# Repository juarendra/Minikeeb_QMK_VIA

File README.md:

# Minikeeb
a split keyboard mini based on microdox and microredox using MX Style Switch 

## Table of Content
* [Product Specsification](#product-specsification)
* [Download VIA](#download-via)
* [Load JSON File](#Load-JSON-File)
* [Link Keycode QMK](#Link-keycode-qmk)
* [Tutorial VIA Usage](#tutorial-via-usage)
* [Cara Setting Knob](#cara-setting-knob)
* [How To use MACRO](#how-to-use-macro)
* [Preview Hardware](#preview-hardware)
* [Preview VIA](#preview-via)
* [Cara Update/Upgrade Firmware](#cara-update/upgrade-firmware)
* [Documentation](#documentation)
  * [Pinout Diagram](#pinout-diagram)
  * [Dimension](#dimension)
  * [BOM](#bom)
  * [Schematic](#schematic)
  * [Example Program](#examples-program)
* [FAQ](#FAQ)

## Product Specsification
- Arduino Pro Micro Type C as Microcontroller
- QMK Firmware
- Support VIA, all key and knob can proggrammed
- RGB per Keys
- 4x Layer 
- Hotswap Switch
- 3D Case 

## Download VIA
Link Download VIA(CHOSEE BASED YOUR OS) : https://github.com/the-via/releases/releases
VIA WEB VERSION : https://usevia.app/

## Link Keycode QMK
- mouse : https://github.com/qmk/qmk_firmware/blob/master/docs/feature_mouse_keys.md
- keyboard : https://github.com/qmk/qmk_firmware/blob/master/docs/keycodes.md

## Tutorial VIA Usage
- https://docs.keeb.io/via

## Cara Setting Knob
- Untuk melakukan setting di knob perlu memasukan command berupa keycode qmk, Jadi cara nya sama dengan melakuykan setting dengan Any key seperti petunjuk pada link berikut: 
https://docs.keeb.io/via

Here's some examples:

- LALT(KC_TAB) - Sends Alt-Tab
- LCTL(KC_C) - Sends Ctrl-C
- LGUI(KC_C) - Sends Cmd-C or Win-C
- LSFT(LCTL(KC_END)) - Sends Shift-Ctrl-End
- MO(1) - Momentarily turn on layer 1
- LCA(KC_DEL) - Sends Ctrl-Alt-Del
- MT(MOD_RSFT, KC_ENT) - Sends Shift if held, Enter if tapped
- MACRO (0) - macro 0

## How To use MACRO
you can read on [this file](https://github.com/juarendra/STREAMPAD-QMK-VIA/blob/main/DOC/MACRO%20VIA%20USAGE.pdf)
or you can read on this [web](https://www.keychron.com/blogs/archived/how-to-use-via-to-program-your-keyboard)
or you can see video [youtube](https://youtu.be/GtSeo69Y0Zw)

## Preview Hardware

## Preview VIA

https://github.com/juarendra/Zeapad-Pro-QMK-VIA/assets/43043633/afd7e68e-0a54-4b18-be12-b96c0f13611a

## Cara Update/Upgrade Firmware
- Siapkan dahulu Keyboard minikeeb, kabel usb dan firmware yang ingin di update/upgrade ke keyboard anda anda
- Anda perlu melakukan flashing di masing masing sisi keyboard (kanan dan kiri)
- Siapkan Firmware yang akan digunakan untuk update/upgrade
- Download Software QMK Toolbox di [link berikut](https://github.com/qmk/qmk_toolbox/releases)
- Install Software QMK Toolbox, Install Semua drivernya. setelah siap anda dapat meload Firmware yang seblumnya. Lalu Centang Auto-Flash seperti gambar dibawah

- Lakukan flashing pada sisi kiri dahulu
- Pada minikeeb sisi kiri Colok kabel ujung usb type C ke keyboard tanpa mencolokannya dahulu ke USB PC anda
- Tekan dan tahan tombol yang berada di ujung atas kiri. lalu colokan Ujung USB yang sebelum ke USB PC anda sambil tetap menahan tombol sebelum nya sebentar
- Setelah ada bunyi/notif USB masuk. anda dapat melepaskan tombol/knobnya
- Maka secara otomatis macropad akan terflash. jika selesai maka tampilan QMK toolbox akan seperti gambar dibawah

- Lakukan flashing pada sisi kanan
- Pada minikeeb sisi kanan Colok kabel ujung usb type C ke keyboard tanpa mencolokannya dahulu ke USB PC anda
- Tekan dan tahan tombol yang berada di ujung atas kanan. lalu colokan Ujung USB yang sebelum ke USB PC anda sambil tetap menahan tombol sebelum nya sebentar
- Setelah ada bunyi/notif USB masuk. anda dapat melepaskan tombol/knobnya
- Maka secara otomatis macropad akan terflash. jika selesai maka tampilan QMK toolbox akan seperti gambar dibawah

## Documentation
### Pinout Diagram
### Dimension
[Dimension File](https://github.com/juarendra/Minikeeb_QMK_VIA/blob/main/HARDWARE/dimension%20minikeeb.pdf)
### BOM
### Schematic
[Schematic File](https://github.com/juarendra/Minikeeb_QMK_VIA/blob/main/HARDWARE/schematic%20minikeeb.pdf)
### Example Program
[Example Firmware]()
## FAQ

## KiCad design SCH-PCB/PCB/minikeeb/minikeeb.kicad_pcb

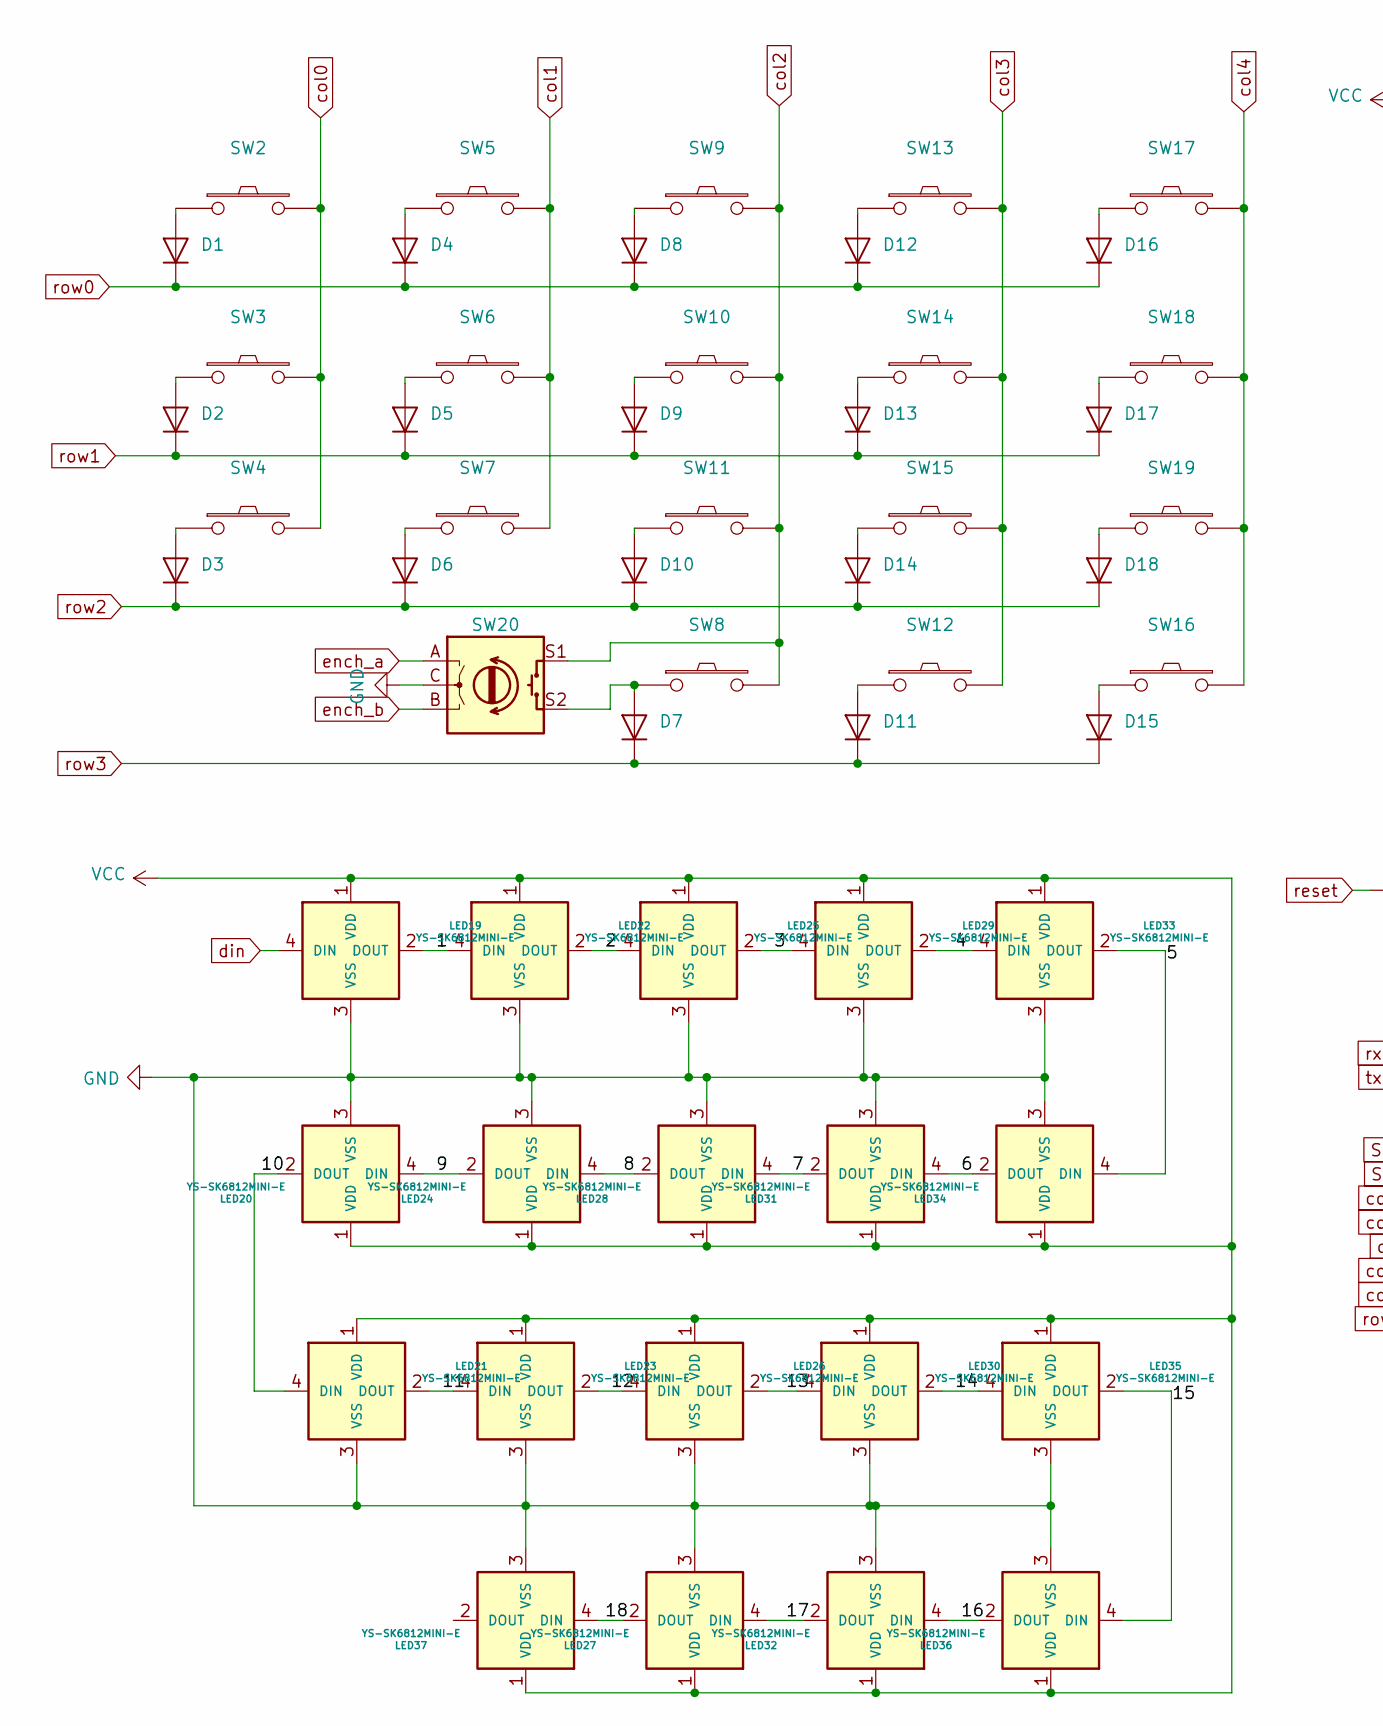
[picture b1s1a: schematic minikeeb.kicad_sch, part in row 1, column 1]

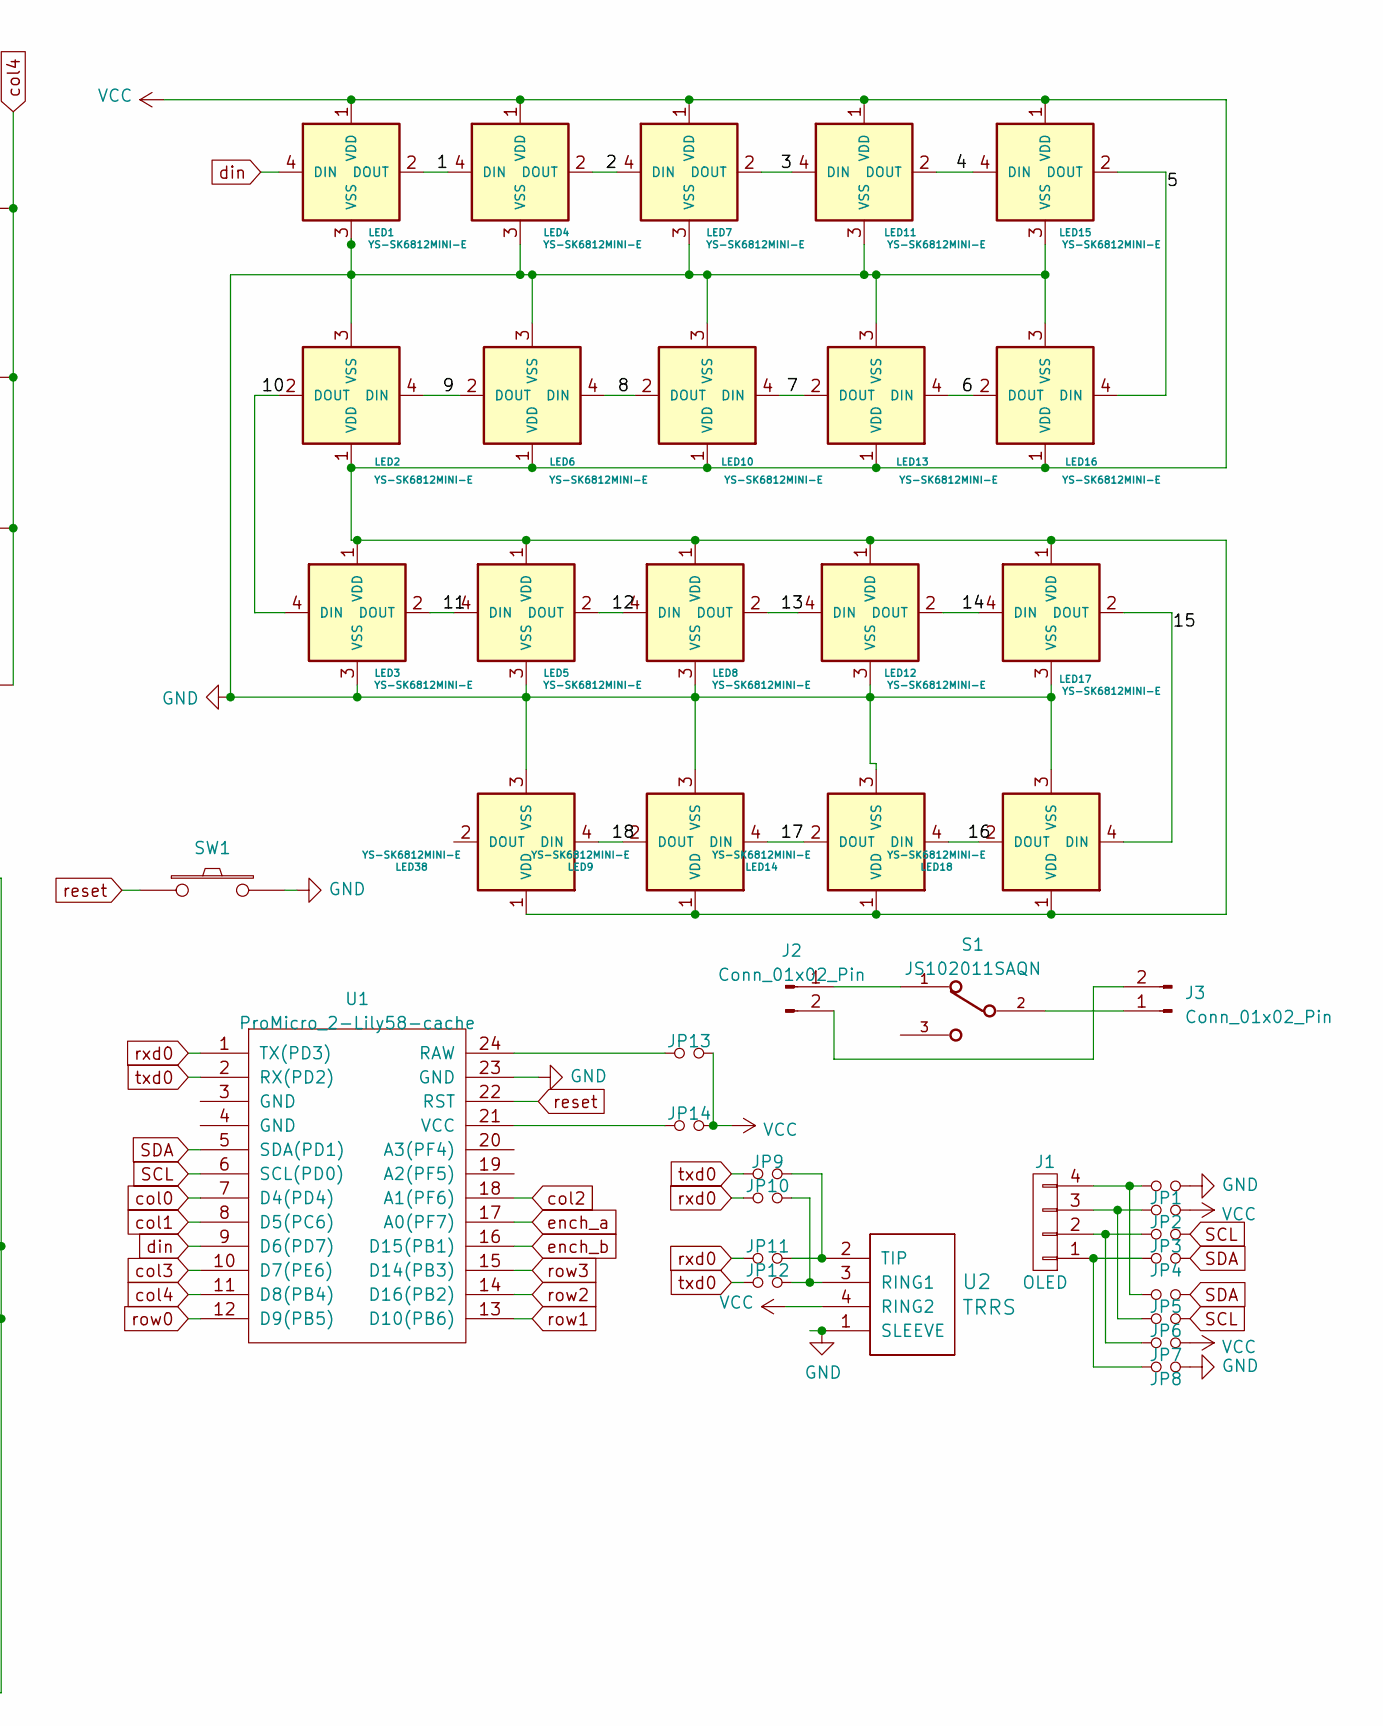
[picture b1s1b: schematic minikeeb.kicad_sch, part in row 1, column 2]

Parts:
D1, D2, D3, D4, D5, D6, D7, D8, D9, D10, D11, D12, D13, D14, D15, D16, D17, D18: D-Lily58-cache; Diode_SOD123
J1: OLED; OLED_4Pin
J2, J3: Conn_01x02_Pin; JST_EH_B2B-EH-A_1x02_P2.50mm_Vertical
JP1, JP2, JP3, JP4, JP5, JP6, JP7, JP8, JP9, JP10, JP11, JP12, JP13, JP14: Jumper_NO_Small; Jumper
LED1, LED2, LED3, LED4, LED5, LED6, LED7, LED8, LED9, LED10, LED11, LED12, LED13, LED14, LED15, LED16, LED17, LED18, LED19, LED20, LED21, LED22, LED23, LED24, LED25, LED26, LED27, LED28, LED29, LED30, LED31, LED32, LED33, LED34, LED35, LED36, LED37, LED38: YS-SK6812MINI-E
S1: JS102011SAQN; SW_JS102011SAQN
SW1: SW_PUSH-Lily58-cache; TACT_SWITCH_TVBP06
SW2, SW3, SW4, SW5, SW6, SW7, SW8, SW9, SW10, SW11, SW12, SW13, SW14, SW15, SW16, SW17, SW18, SW19: SW_PUSH-Lily58-cache; CherryMX_Hotswap
SW20: Rotary_Encoder_Switch-Device; RotaryEncoder_Alps_EC11E-Switch_Vertical_H20mm-keebio_modif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
U1: ProMicro_2-Lily58-cache; ArduinoProMicro-ZigZag-DoubleSided
U2: TRRS; MJ-4PP-9

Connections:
/1: LED1.2 (DOUT), LED4.4 (DIN), LED19.2 (DOUT), LED22.4 (DIN)
/2: LED4.2 (DOUT), LED7.4 (DIN), LED22.2 (DOUT), LED25.4 (DIN)
/3: LED7.2 (DOUT), LED11.4 (DIN), LED25.2 (DOUT), LED29.4 (DIN)
/4: LED11.2 (DOUT), LED15.4 (DIN), LED29.2 (DOUT), LED33.4 (DIN)
/5: LED15.2 (DOUT), LED16.4 (DIN), LED33.2 (DOUT), LED34.4 (DIN)
/6: LED13.4 (DIN), LED16.2 (DOUT), LED31.4 (DIN), LED34.2 (DOUT)
/7: LED10.4 (DIN), LED13.2 (DOUT), LED28.4 (DIN), LED31.2 (DOUT)
/8: LED6.4 (DIN), LED10.2 (DOUT), LED24.4 (DIN), LED28.2 (DOUT)
/9: LED2.4 (DIN), LED6.2 (DOUT), LED20.4 (DIN), LED24.2 (DOUT)
/10: LED2.2 (DOUT), LED3.4 (DIN), LED20.2 (DOUT), LED21.4 (DIN); also elsewhere on the board
/11: LED3.2 (DOUT), LED5.4 (DIN), LED21.2 (DOUT), LED23.4 (DIN); also elsewhere on the board
/12: LED5.2 (DOUT), LED8.4 (DIN), LED23.2 (DOUT), LED26.4 (DIN)
/13: LED8.2 (DOUT), LED12.4 (DIN), LED26.2 (DOUT), LED30.4 (DIN)
/14: LED12.2 (DOUT), LED17.4 (DIN), LED30.2 (DOUT), LED35.4 (DIN)
/15: LED17.2 (DOUT), LED18.4 (DIN), LED35.2 (DOUT), LED36.4 (DIN)
/16: LED14.4 (DIN), LED18.2 (DOUT), LED32.4 (DIN), LED36.2 (DOUT)
/17: LED9.4 (DIN), LED14.2 (DOUT), LED27.4 (DIN), LED32.2 (DOUT)
/18: LED9.2 (DOUT), LED27.2 (DOUT), LED37.4 (DIN), LED38.4 (DIN)
GND: JP1.2, JP8.2, LED1.3 (VSS), LED2.3 (VSS), LED3.3 (VSS), LED4.3 (VSS), LED5.3 (VSS), LED6.3 (VSS), LED7.3 (VSS), LED8.3 (VSS), LED9.3 (VSS), LED10.3 (VSS), LED11.3 (VSS), LED12.3 (VSS), LED13.3 (VSS), LED14.3 (VSS), LED15.3 (VSS), LED16.3 (VSS), LED17.3 (VSS), LED18.3 (VSS), LED19.3 (VSS), LED20.3 (VSS), LED21.3 (VSS), LED22.3 (VSS), LED23.3 (VSS), LED24.3 (VSS), LED25.3 (VSS), LED26.3 (VSS), LED27.3 (VSS), LED28.3 (VSS), LED29.3 (VSS), LED30.3 (VSS), LED31.3 (VSS), LED32.3 (VSS), LED33.3 (VSS), LED34.3 (VSS), LED35.3 (VSS), LED36.3 (VSS), LED37.3 (VSS), LED38.3 (VSS), SW1.2, SW20.C, U1.23 (GND), U2.1 (SLEEVE); also elsewhere on the board
unnamed: D1.2 (A), SW2.1
unnamed: D2.2 (A), SW3.1
unnamed: D3.2 (A), SW4.1
unnamed: D4.2 (A), SW5.1
unnamed: D5.2 (A), SW6.1
unnamed: D6.2 (A), SW7.1
unnamed: D7.2 (A), SW8.1, SW20.S2
unnamed: D8.2 (A), SW9.1
unnamed: D9.2 (A), SW10.1
unnamed: D10.2 (A), SW11.1
unnamed: D11.2 (A), SW12.1
unnamed: D12.2 (A), SW13.1
unnamed: D13.2 (A), SW14.1
unnamed: D14.2 (A), SW15.1
unnamed: D15.2 (A), SW16.1
unnamed: D16.2 (A), SW17.1
unnamed: D17.2 (A), SW18.1
unnamed: D18.2 (A), SW19.1
unnamed: J1.1, JP4.1, JP8.1
unnamed: J1.2, JP3.1, JP7.1
unnamed: J1.3, JP2.1, JP6.1
unnamed: J1.4, JP1.1, JP5.1
unnamed: J2.1, S1.1
unnamed: J2.2, J3.2
unnamed: J3.1, S1.2
unnamed: JP13.2, U1.24 (RAW)
unnamed: JP14.2, U1.21 (VCC)
unnamed: JP10.1, JP12.1, U2.3 (RING1)
unnamed: JP9.1, JP11.1, U2.2 (TIP)
SCL: JP3.2, JP6.2, U1.6 (SCL(PD0))
SDA: JP4.2, JP5.2, U1.5 (SDA(PD1))
VCC: JP2.2, JP7.2, JP13.1, JP14.1, LED1.1 (VDD), LED2.1 (VDD), LED3.1 (VDD), LED4.1 (VDD), LED5.1 (VDD), LED6.1 (VDD), LED7.1 (VDD), LED8.1 (VDD), LED9.1 (VDD), LED10.1 (VDD), LED11.1 (VDD), LED12.1 (VDD), LED13.1 (VDD), LED14.1 (VDD), LED15.1 (VDD), LED16.1 (VDD), LED17.1 (VDD), LED18.1 (VDD), LED19.1 (VDD), LED20.1 (VDD), LED22.1 (VDD), LED23.1 (VDD), LED24.1 (VDD), LED25.1 (VDD), LED26.1 (VDD), LED27.1 (VDD), LED28.1 (VDD), LED29.1 (VDD), LED30.1 (VDD), LED31.1 (VDD), LED32.1 (VDD), LED33.1 (VDD), LED34.1 (VDD), LED35.1 (VDD), LED36.1 (VDD), LED37.1 (VDD), LED38.1 (VDD), U2.4 (RING2); also elsewhere on the board
col0: SW2.2, SW3.2, SW4.2, U1.7 (D4(PD4))
col1: SW5.2, SW6.2, SW7.2, U1.8 (D5(PC6))
col2: SW8.2, SW9.2, SW10.2, SW11.2, SW20.S1, U1.18 (A1(PF6))
col3: SW12.2, SW13.2, SW14.2, SW15.2, U1.10 (D7(PE6))
col4: SW16.2, SW17.2, SW18.2, SW19.2, U1.11 (D8(PB4))
din: LED1.4 (DIN), LED19.4 (DIN), U1.9 (D6(PD7))
ench_a: SW20.A, U1.17 (A0(PF7))
ench_b: SW20.B, U1.16 (D15(PB1))
reset: SW1.1, U1.22 (RST)
row0: D1.1 (K), D4.1 (K), D8.1 (K), D12.1 (K), D16.1 (K), U1.12 (D9(PB5))
row1: D2.1 (K), D5.1 (K), D9.1 (K), D13.1 (K), D17.1 (K), U1.13 (D10(PB6))
row2: D3.1 (K), D6.1 (K), D10.1 (K), D14.1 (K), D18.1 (K), U1.14 (D16(PB2))
row3: D7.1 (K), D11.1 (K), D15.1 (K), U1.15 (D14(PB3))
rxd0: JP10.2, JP11.2, U1.1 (TX(PD3))
txd0: JP9.2, JP12.2, U1.2 (RX(PD2))

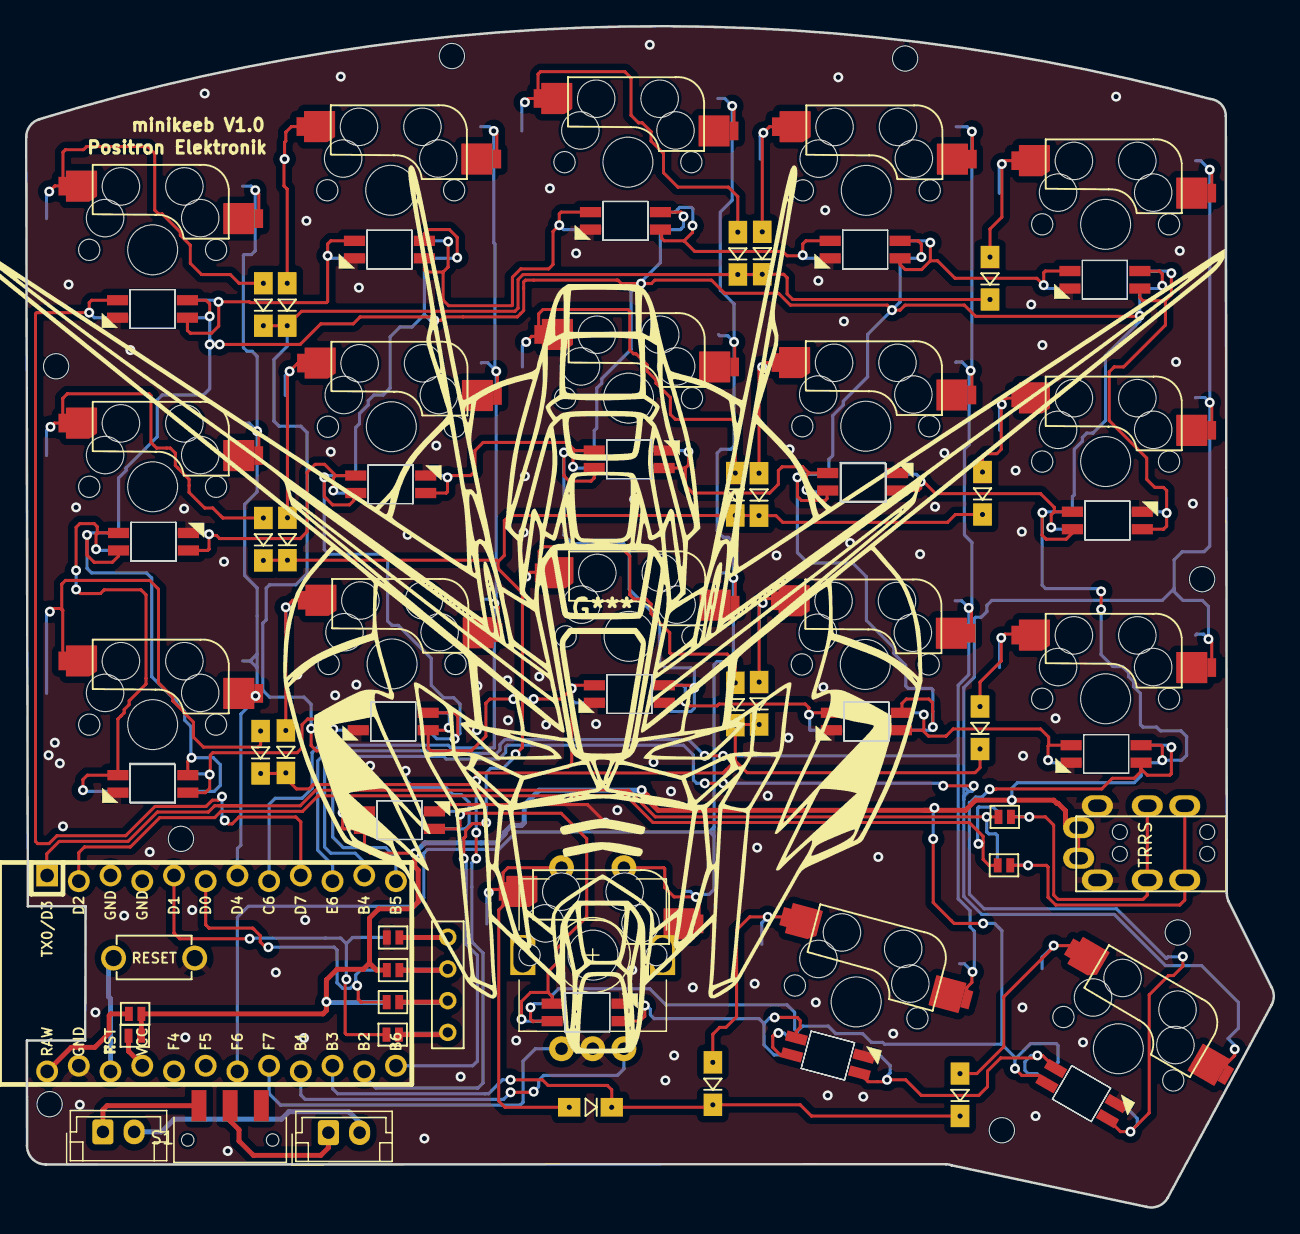
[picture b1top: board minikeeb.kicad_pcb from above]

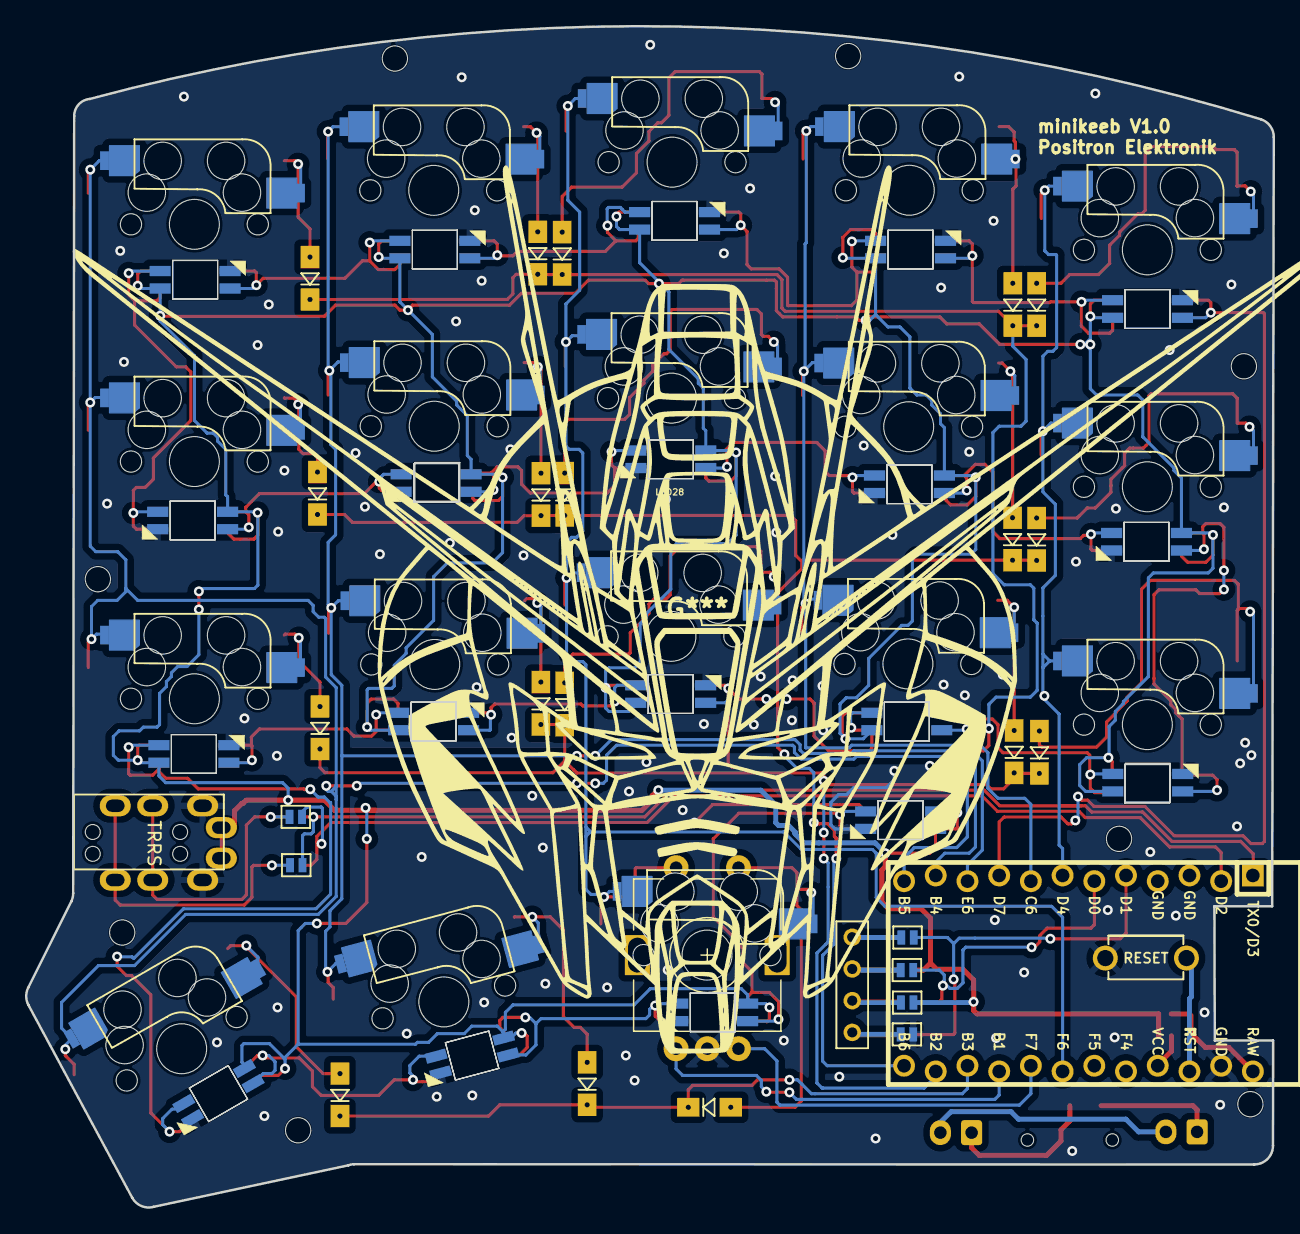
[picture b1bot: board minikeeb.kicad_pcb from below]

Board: 2 copper layers, 99.9 x 94.6 mm, 96 parts (26 on the bottom side), 66 nets.

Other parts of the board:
locked: YS-SK6812MINI-E

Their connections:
/10: locked.4 (DIN); also elsewhere on the board
/11: locked.2 (DOUT); also elsewhere on the board
GND: locked.3 (VSS); also elsewhere on the board
VCC: locked.1 (VDD); also elsewhere on the board

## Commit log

2024-08-29 FEAT: add firt pcb and sch design file
2024-09-01 DOC: update readme
2024-09-01 FEAT: updaet PCB
2024-09-03 FEAT: change microcontroller to promicro layout
2024-09-03 FEAT: add logo and name
2024-09-03 FEAT: add file render 3d pcb
2024-09-03 FEAT: add bolt hole
2024-09-05 FEAT: update pcb
2024-09-08 FEAT: update pcb for vcc selection
2024-09-17 FEAT: add 3d file plate
2024-09-17 FEAT: add image 3d pcb with plate
2024-09-17 FEAT: add image 3d pcb with componnet
2024-09-18 FEAT : update hole for plate design
2024-10-18 FIX fix dimension PCB
2024-10-31 FEAT: update keyboard pcb case and documentation
2024-10-31 FEAT: add image doc
2024-10-31 DOC: add dimension file and schematic
2024-10-31 FEAT: add gerber file
2024-10-31 FEAT: add pcb image
2024-10-31 FEAT: update
